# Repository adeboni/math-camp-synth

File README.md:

# Burning Man Math Camp Synths
2022: Pendulum

2023: Jukebox

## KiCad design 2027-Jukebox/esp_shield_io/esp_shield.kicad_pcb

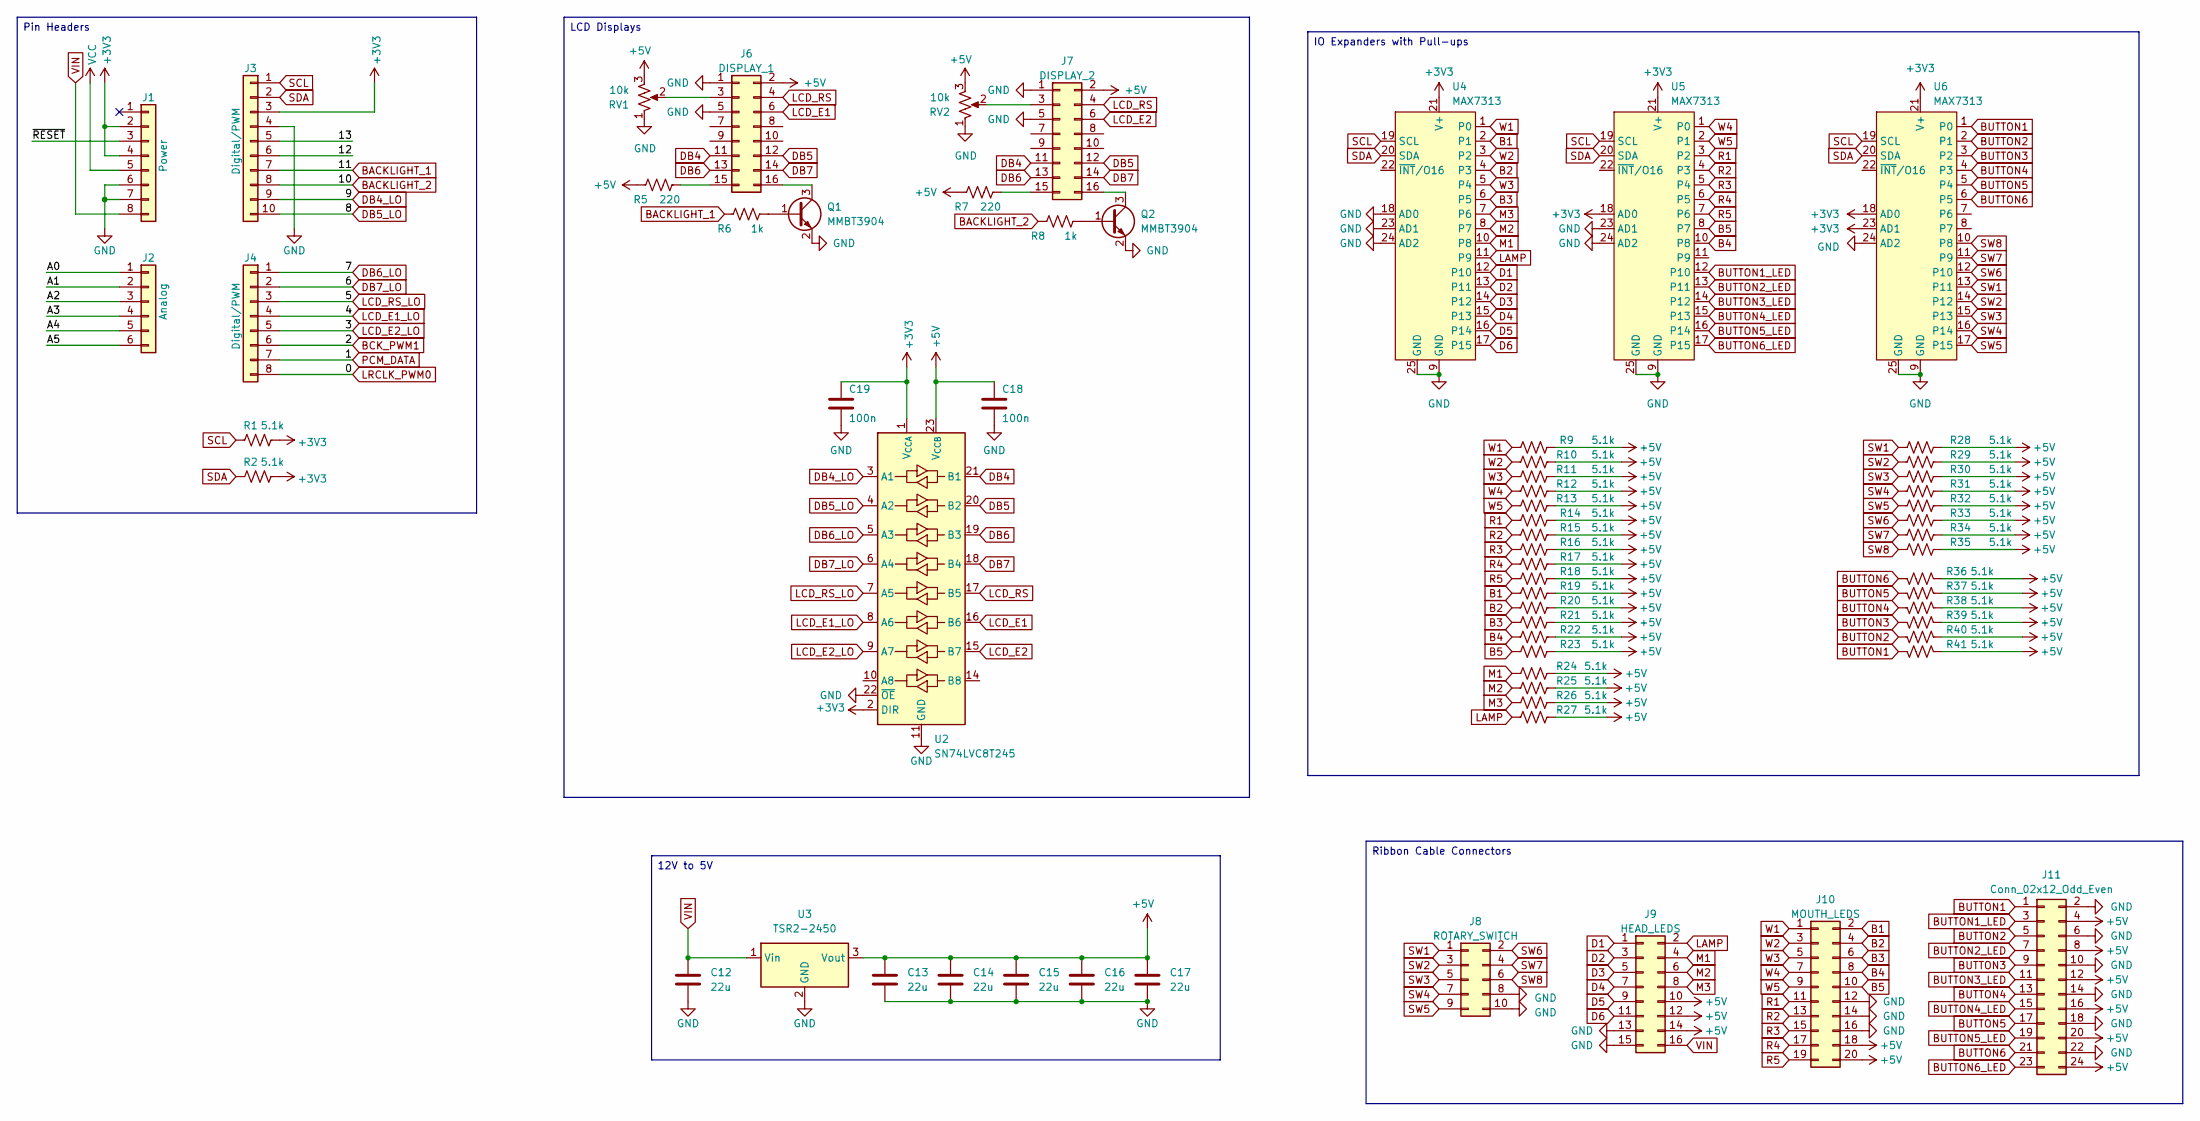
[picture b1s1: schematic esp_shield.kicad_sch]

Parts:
C12, C13, C14, C15, C16, C17: 22u; C_1206_3216Metric
C18, C19: 100n; C_0603_1608Metric
J1: Power; PinSocket_1x08_P2.54mm_Vertical
J2: Analog; PinSocket_1x06_P2.54mm_Vertical
J3: Digital/PWM; PinSocket_1x10_P2.54mm_Vertical
J4: Digital/PWM; PinSocket_1x08_P2.54mm_Vertical
J6: DISPLAY_1; IDC-Header_2x08_P2.54mm_Vertical
J7: DISPLAY_2; IDC-Header_2x08_P2.54mm_Vertical
J8: ROTARY_SWITCH; IDC-Header_2x05_P2.54mm_Vertical
J9: HEAD_LEDS; IDC-Header_2x08_P2.54mm_Vertical
J10: MOUTH_LEDS; IDC-Header_2x10_P2.54mm_Vertical
J11: Conn_02x12_Odd_Even; IDC-Header_2x12_P2.54mm_Vertical
Q1, Q2: MMBT3904; SOT-23
R1, R2, R9, R10, R11, R12, R13, R14, R15, R16, R17, R18, R19, R20, R21, R22, R23, R24, R25, R26, R27, R28, R29, R30, R31, R32, R33, R34, R35, R36, R37, R38, R39, R40, R41: 5.1k; R_0603_1608Metric
R5, R7: 220; R_0603_1608Metric
R6, R8: 1k; R_0603_1608Metric
RV1, RV2: 10k; Potentiometer_Bourns_3314G_Vertical
U2: SN74LVC8T245; TSSOP-24_4.4x7.8mm_P0.65mm
U3: TSR2-2450; Converter_DCDC_TRACO_TSR2-xxxx_THT
U4, U5, U6: MAX7313; TQFN-24-1EP_4x4mm_P0.5mm_EP2.6x2.6mm_ThermalVias

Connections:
+3V3: C19.1, J1.2, J1.4, J3.3, R1.2, R2.2, U2.1 (V_{CCA}), U2.2 (DIR), U4.21 (V+), U5.18 (AD0), U5.21 (V+), U6.18 (AD0), U6.21 (V+), U6.23 (AD1)
+5V: C13.1, C14.1, C15.1, C16.1, C17.1, C18.1, J6.2, J7.2, J9.10, J9.12, J9.14, J10.18, J10.20, J11.4, J11.8, J11.12, J11.16, J11.20, J11.24, R5.1, R7.1, R9.2, R10.2, R11.2, R12.2, R13.2, R14.2, R15.2, R16.2, R17.2, R18.2, R19.2, R20.2, R21.2, R22.2, R23.2, R24.2, R25.2, R26.2, R27.2, R28.2, R29.2, R30.2, R31.2, R32.2, R33.2, R34.2, R35.2, R36.2, R37.2, R38.2, R39.2, R40.2, R41.2, RV1.3, RV2.3, U2.23 (V_{CCB}), U2.24 (V_{CCB}), U3.3 (Vout)
/12: J3.6
/13: J3.5
/A0: J2.1
/A1: J2.2
/A2: J2.3
/A3: J2.4
/A4: J2.5
/A5: J2.6
/~RESET: J1.3
B1: J10.2, R19.1, U4.2 (P1)
B2: J10.4, R20.1, U4.4 (P3)
B3: J10.6, R21.1, U4.6 (P5)
B4: J10.8, R22.1, U5.10 (P8)
B5: J10.10, R23.1, U5.8 (P7)
BACKLIGHT_1: J3.7, R6.1
BACKLIGHT_2: J3.8, R8.1
BCK_PWM1: J4.6
BUTTON1: J11.1, R41.1, U6.1 (P0)
BUTTON1_LED: J11.3, U5.12 (P10)
BUTTON2: J11.5, R40.1, U6.2 (P1)
BUTTON2_LED: J11.7, U5.13 (P11)
BUTTON3: J11.9, R39.1, U6.3 (P2)
BUTTON3_LED: J11.11, U5.14 (P12)
BUTTON4: J11.13, R38.1, U6.4 (P3)
BUTTON4_LED: J11.15, U5.15 (P13)
BUTTON5: J11.17, R37.1, U6.5 (P4)
BUTTON5_LED: J11.19, U5.16 (P14)
BUTTON6: J11.21, R36.1, U6.6 (P5)
BUTTON6_LED: J11.23, U5.17 (P15)
D1: J9.1, U4.12 (P10)
D2: J9.3, U4.13 (P11)
D3: J9.5, U4.14 (P12)
D4: J9.7, U4.15 (P13)
D5: J9.9, U4.16 (P14)
D6: J9.11, U4.17 (P15)
DB4: J6.11, J7.11, U2.21 (B1)
DB4_LO: J3.9, U2.3 (A1)
DB5: J6.12, J7.12, U2.20 (B2)
DB5_LO: J3.10, U2.4 (A2)
DB6: J6.13, J7.13, U2.19 (B3)
DB6_LO: J4.1, U2.5 (A3)
DB7: J6.14, J7.14, U2.18 (B4)
DB7_LO: J4.2, U2.6 (A4)
GND: C12.2, C13.2, C14.2, C15.2, C16.2, C17.2, C18.2, C19.2, J1.6, J1.7, J3.4, J6.1, J6.5, J7.1, J7.5, J8.8, J8.10, J9.13, J9.15, J10.12, J10.14, J10.16, J11.2, J11.6, J11.10, J11.14, J11.18, J11.22, Q1.2 (E), Q2.2 (E), RV1.1, RV2.1, U2.11 (GND), U2.12 (GND), U2.13 (GND), U2.22 (~OE), U3.2 (GND), U4.9 (GND), U4.18 (AD0), U4.23 (AD1), U4.24 (AD2), U4.25 (GND), U5.9 (GND), U5.23 (AD1), U5.24 (AD2), U5.25 (GND), U6.9 (GND), U6.24 (AD2), U6.25 (GND)
LAMP: J9.2, R27.1, U4.11 (P9)
LCD_E1: J6.6, U2.16 (B6)
LCD_E1_LO: J4.4, U2.8 (A6)
LCD_E2: J7.6, U2.15 (B7)
LCD_E2_LO: J4.5, U2.9 (A7)
LCD_RS: J6.4, J7.4, U2.17 (B5)
LCD_RS_LO: J4.3, U2.7 (A5)
LRCLK_PWM0: J4.8
M1: J9.4, R24.1, U4.10 (P8)
M2: J9.6, R25.1, U4.8 (P7)
M3: J9.8, R26.1, U4.7 (P6)
unnamed: J6.3, RV1.2
unnamed: J6.15, R5.2
unnamed: J6.16, Q1.3 (C)
unnamed: J7.3, RV2.2
unnamed: J7.15, R7.2
unnamed: J7.16, Q2.3 (C)
unnamed: Q1.1 (B), R6.2
unnamed: Q2.1 (B), R8.2
PCM_DATA: J4.7
R1: J10.11, R14.1, U5.3 (P2)
R2: J10.13, R15.1, U5.4 (P3)
R3: J10.15, R16.1, U5.5 (P4)
R4: J10.17, R17.1, U5.6 (P5)
R5: J10.19, R18.1, U5.7 (P6)
SCL: J3.1, R1.1, U4.19 (SCL), U5.19 (SCL), U6.19 (SCL)
SDA: J3.2, R2.1, U4.20 (SDA), U5.20 (SDA), U6.20 (SDA)
SW1: J8.1, R28.1, U6.13 (P11)
SW2: J8.3, R29.1, U6.14 (P12)
SW3: J8.5, R30.1, U6.15 (P13)
SW4: J8.7, R31.1, U6.16 (P14)
SW5: J8.9, R32.1, U6.17 (P15)
SW6: J8.2, R33.1, U6.12 (P10)
SW7: J8.4, R34.1, U6.11 (P9)
SW8: J8.6, R35.1, U6.10 (P8)
VCC: J1.5
VIN: C12.1, J1.8, J9.16, U3.1 (Vin)
W1: J10.1, R9.1, U4.1 (P0)
W2: J10.3, R10.1, U4.3 (P2)
W3: J10.5, R11.1, U4.5 (P4)
W4: J10.7, R12.1, U5.1 (P0)
W5: J10.9, R13.1, U5.2 (P1)

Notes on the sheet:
Ribbon Cable Connectors
LCD Displays
IO Expanders with Pull-ups
12V to 5V
Pin Headers

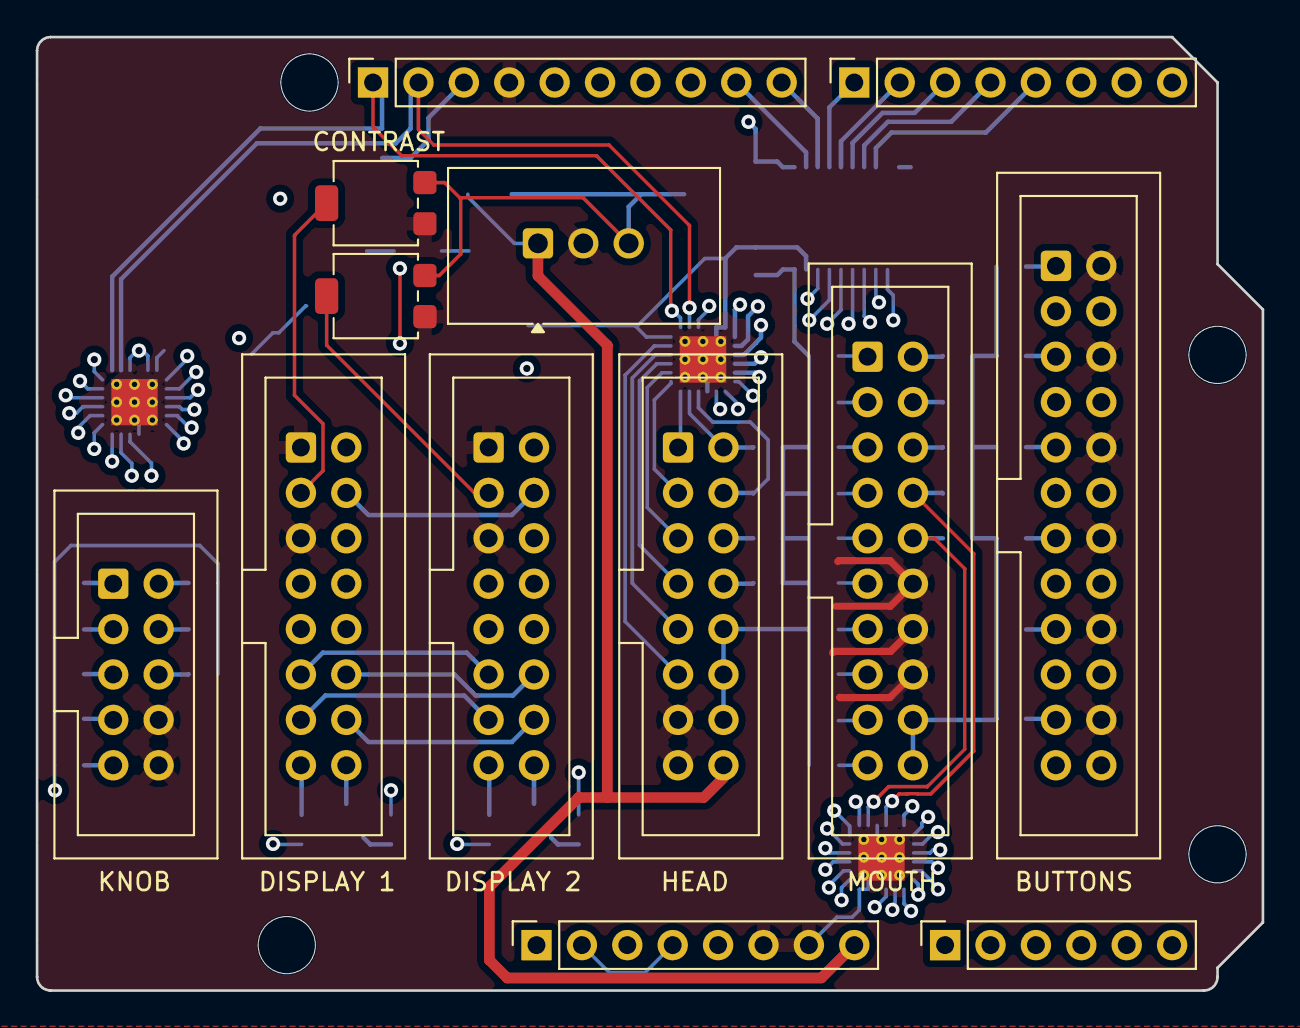
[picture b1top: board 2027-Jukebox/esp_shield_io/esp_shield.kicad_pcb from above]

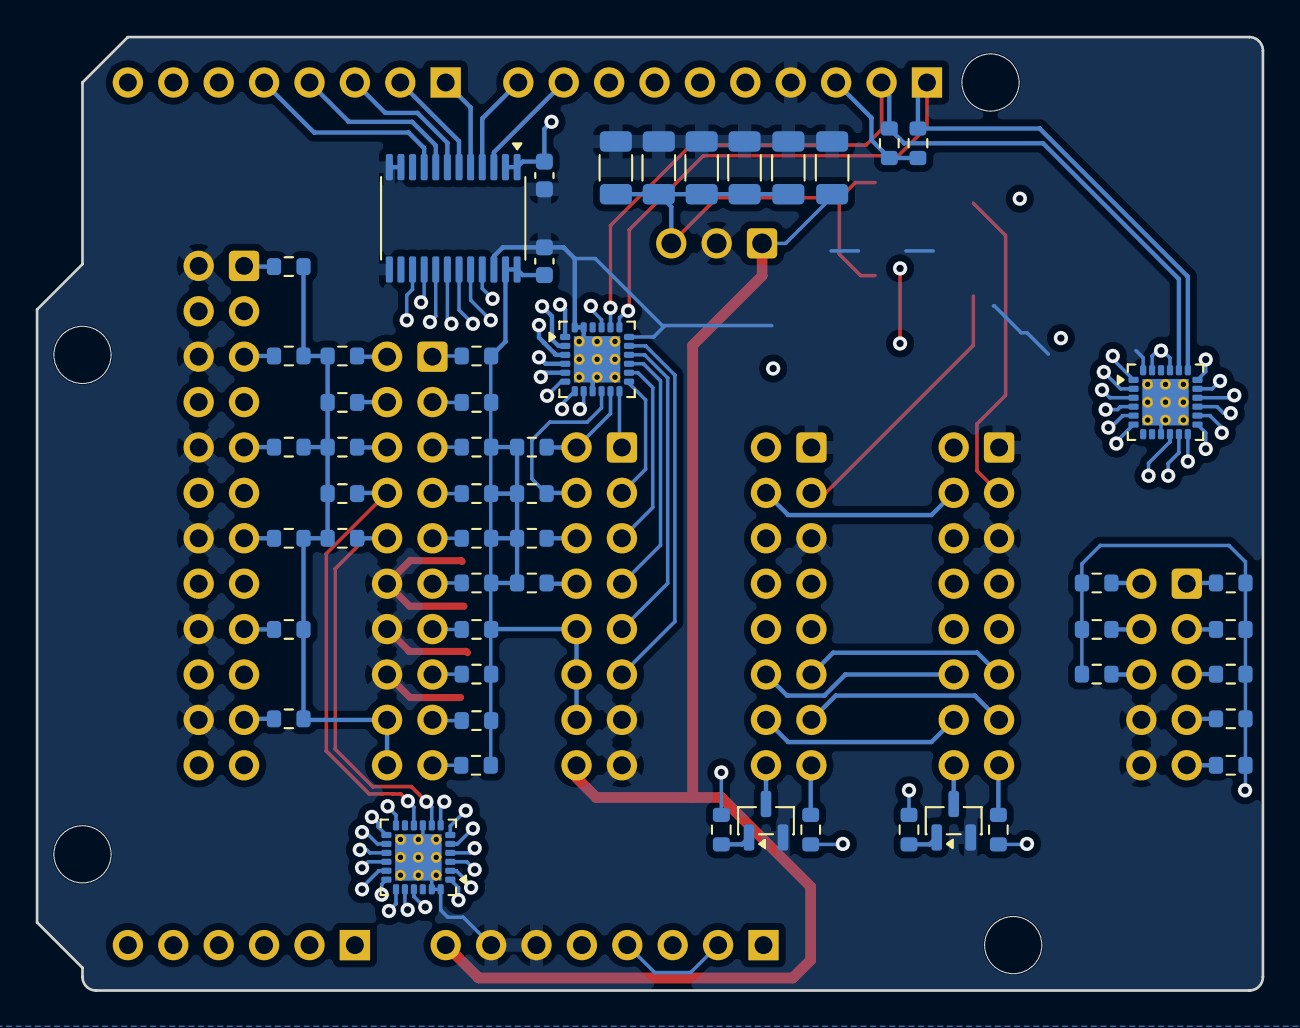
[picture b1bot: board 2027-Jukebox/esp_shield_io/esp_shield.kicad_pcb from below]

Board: 4 copper layers, 68.6 x 53.3 mm, 70 parts (53 on the bottom side), 75 nets.

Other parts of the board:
MH1, MH2, MH3, MH4: MountingHole_3.2mm

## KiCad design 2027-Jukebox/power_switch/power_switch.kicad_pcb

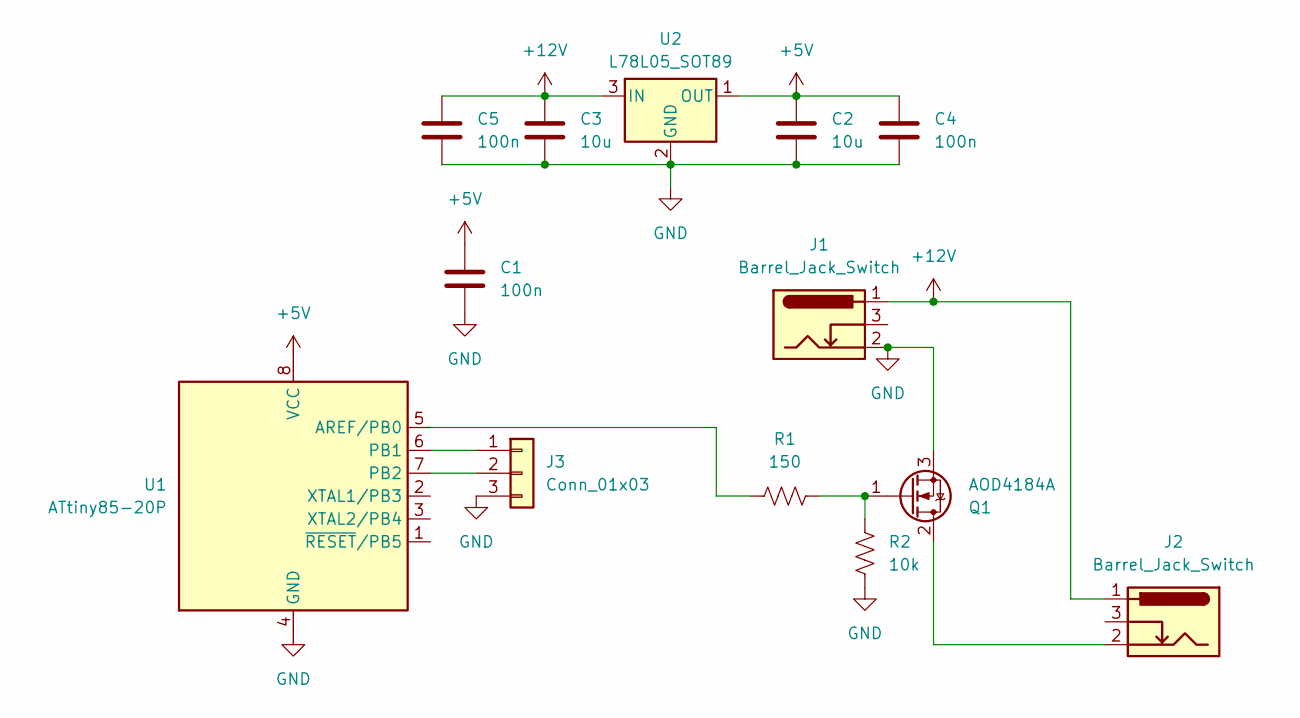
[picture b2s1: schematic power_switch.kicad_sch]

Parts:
C1, C4, C5: 100n; C_0603_1608Metric
C2, C3: 10u; C_0603_1608Metric
J1, J2: Barrel_Jack_Switch; BarrelJack_Horizontal
J3: Conn_01x03; JST_XH_S3B-XH-A_1x03_P2.50mm_Horizontal
Q1: AOD4184A; TO-252-2
R1: 150; R_0603_1608Metric
R2: 10k; R_0603_1608Metric
U1: ATtiny85-20P; DIP-8_W7.62mm
U2: L78L05_SOT89; SOT-89-3

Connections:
+5V: C1.1, C2.1, C4.1, U1.8 (VCC), U2.1 (OUT)
+12V: C3.1, C5.1, J1.1, J2.1, U2.3 (IN)
GND: C1.2, C2.2, C3.2, C4.2, C5.2, J1.2, J3.3, Q1.3 (S), R2.1, U1.4 (GND), U2.2 (GND)
unnamed: J3.1, U1.6 (PB1)
unnamed: J3.2, U1.7 (PB2)
unnamed: J2.2, Q1.2 (D)
unnamed: Q1.1 (G), R1.2, R2.2
unnamed: R1.1, U1.5 (AREF/PB0)

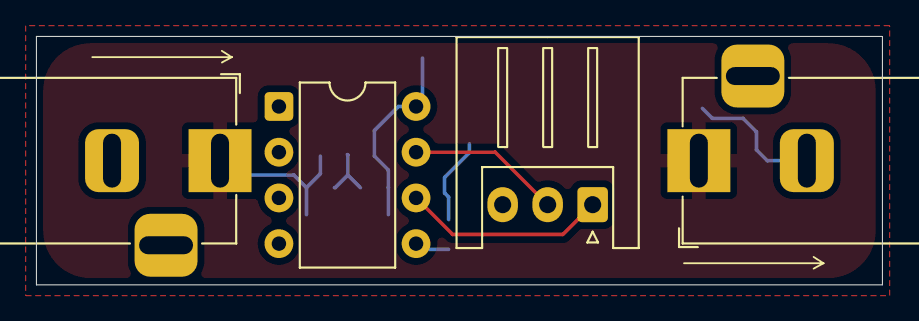
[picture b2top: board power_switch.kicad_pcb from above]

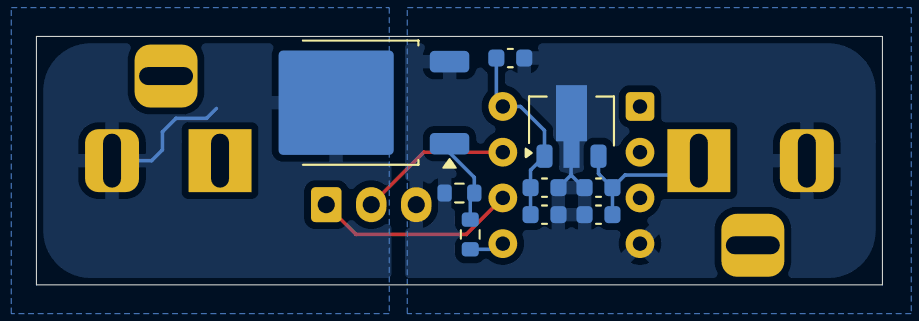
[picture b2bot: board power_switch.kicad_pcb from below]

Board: 2 copper layers, 47.0 x 13.8 mm, 13 parts (9 on the bottom side), 8 nets.

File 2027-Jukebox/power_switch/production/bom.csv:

Designator,Footprint,Quantity,Value,LCSC Part #
"C1, C4, C5",0603,3,100n,
"C2, C3",0603,2,10u,
"J1, J2",BarrelJack_Horizontal,2,Barrel_Jack_Switch,
J3,JST_XH_S3B-XH-A_1x03_P2.50mm_Horizontal,1,Conn_01x03,
Q1,TO-252-2,1,AOD4184A,
R1,0603,1,150,
R2,0603,1,10k,
U1,DIP-8_W7.62mm,1,ATtiny85-20P,
U2,SOT-89-3,1,L78L05_SOT89,

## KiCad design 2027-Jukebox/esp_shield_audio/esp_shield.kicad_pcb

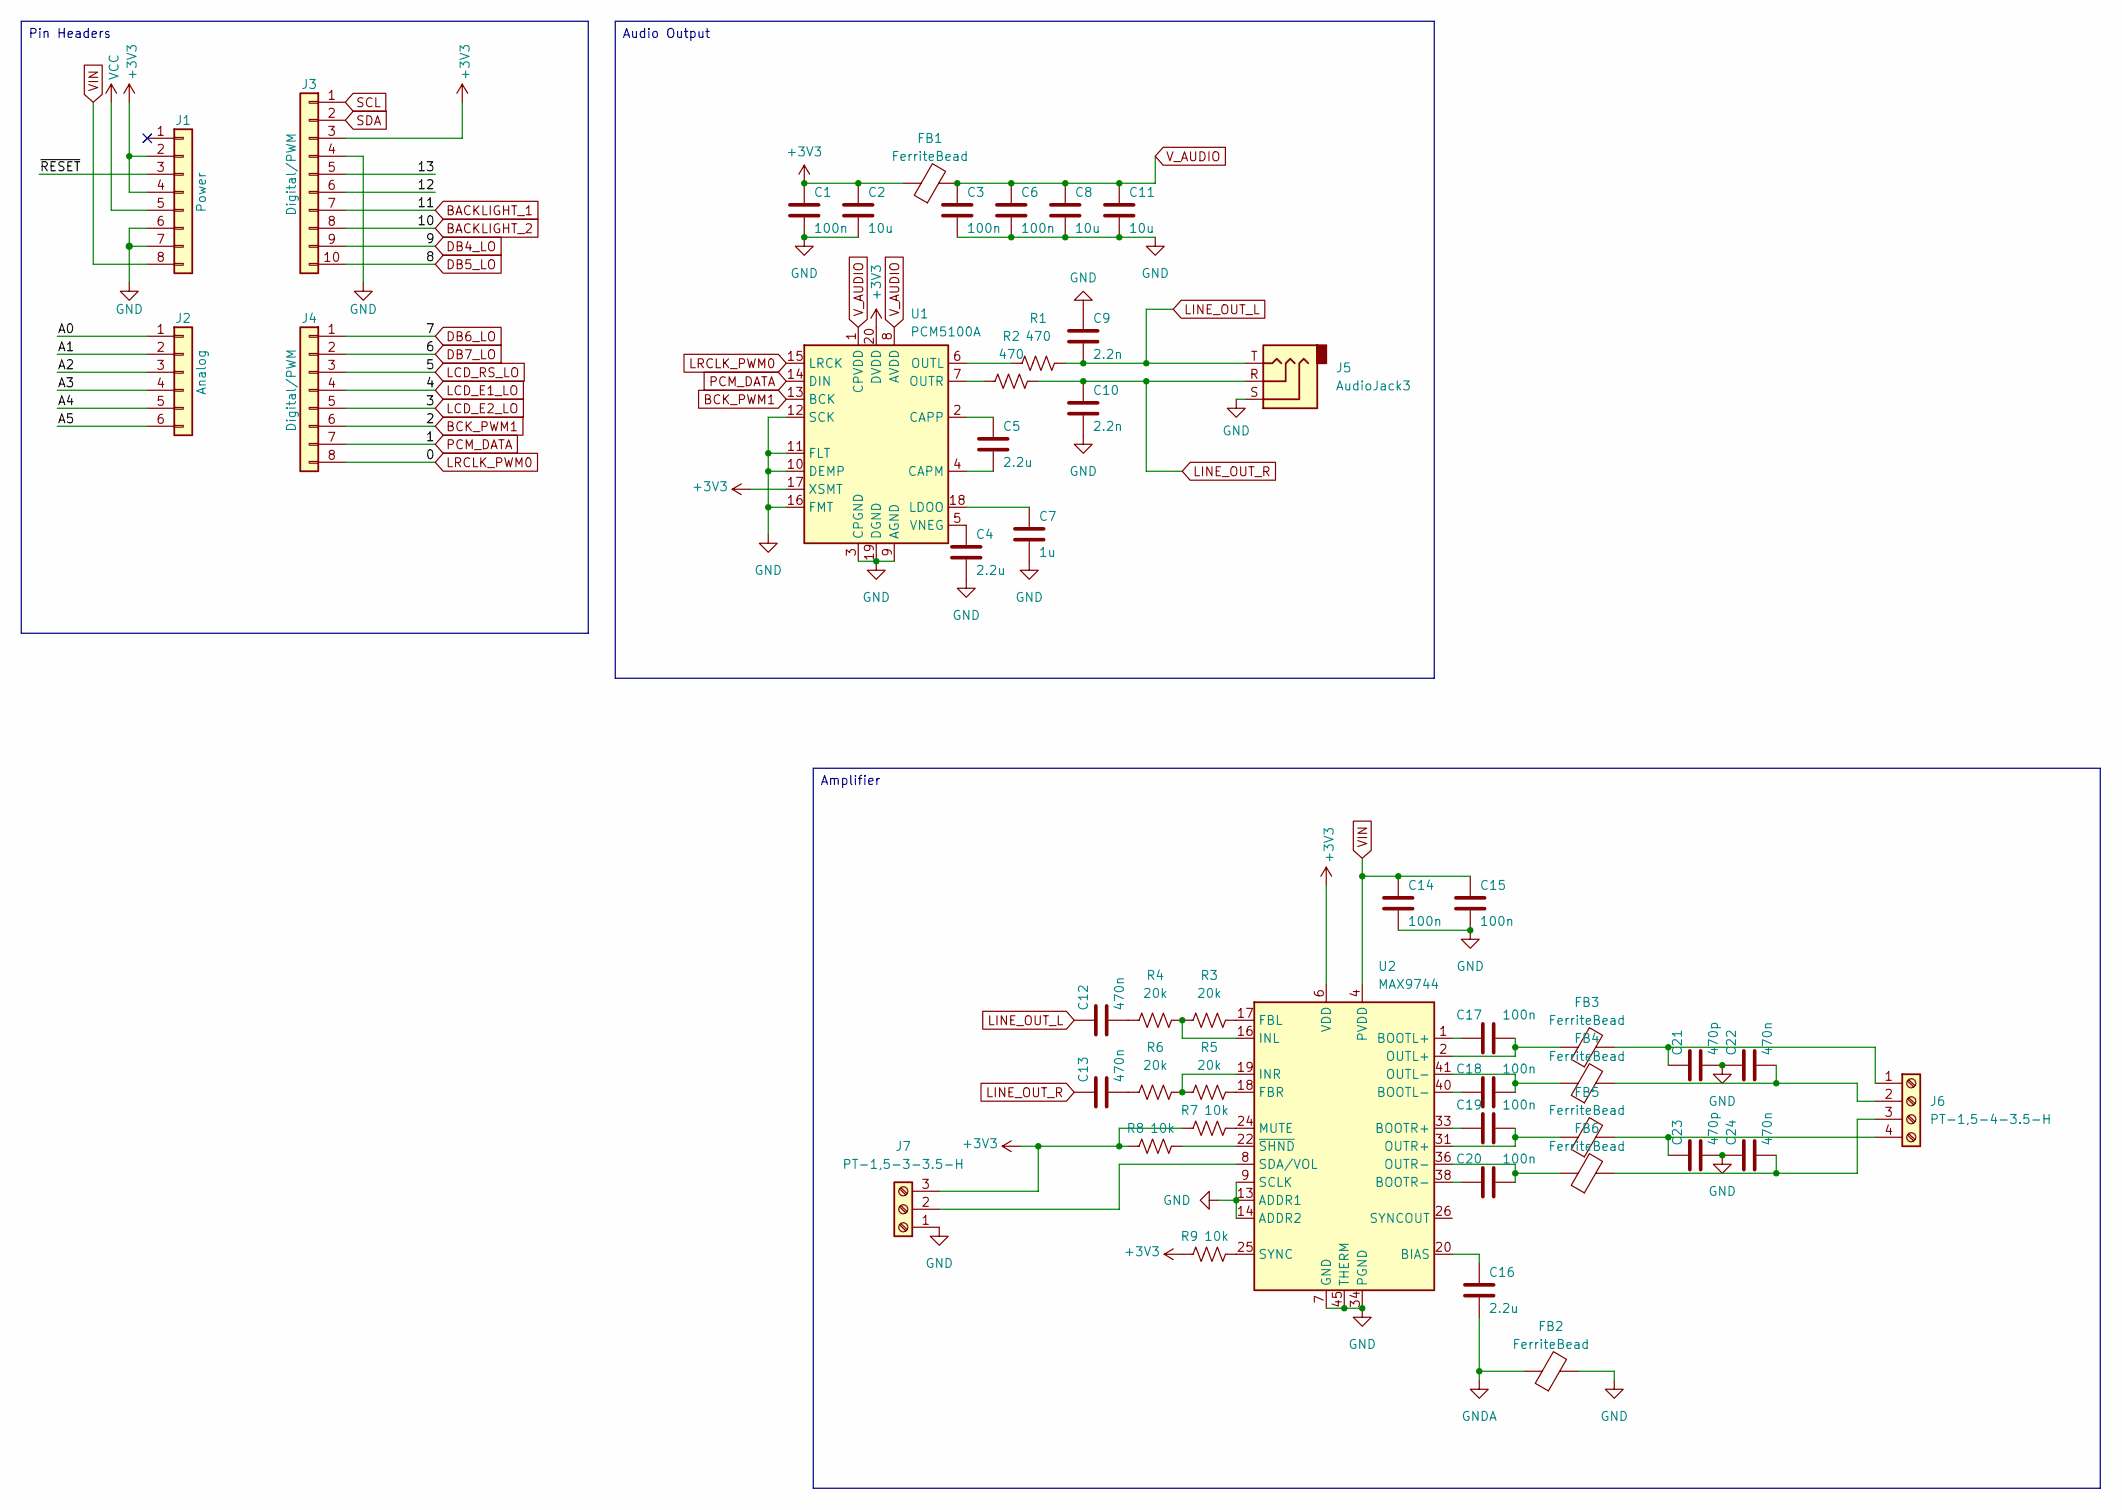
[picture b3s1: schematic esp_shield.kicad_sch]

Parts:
C1, C3, C6, C14, C15, C17, C18, C19, C20: 100n; C_0603_1608Metric
C2, C8, C11: 10u; C_0603_1608Metric
C4, C5, C16: 2.2u; C_0603_1608Metric
C7: 1u; C_0603_1608Metric
C9, C10: 2.2n; C_0603_1608Metric
C12, C13, C22, C24: 470n; C_0603_1608Metric
C21, C23: 470p; C_0603_1608Metric
FB1, FB2, FB3, FB4, FB5, FB6: FerriteBead; L_0603_1608Metric
J1: Power; PinSocket_1x08_P2.54mm_Vertical
J2: Analog; PinSocket_1x06_P2.54mm_Vertical
J3: Digital/PWM; PinSocket_1x10_P2.54mm_Vertical
J4: Digital/PWM; PinSocket_1x08_P2.54mm_Vertical
J5: AudioJack3; Jack_3.5mm_CUI_SJ-3523-SMT_Horizontal
J6: PT-1,5-4-3.5-H; TerminalBlock_Phoenix_PT-1,5-4-3.5-H_1x04_P3.50mm_Horizontal
J7: PT-1,5-3-3.5-H; TerminalBlock_Phoenix_PT-1,5-3-3.5-H_1x03_P3.50mm_Horizontal
R1, R2: 470; R_0603_1608Metric
R3, R4, R5, R6: 20k; R_0603_1608Metric
R7, R8, R9: 10k; R_0603_1608Metric
U1: PCM5100A; TSSOP-20_4.4x6.5mm_P0.65mm
U2: MAX9744; TQFN-44-1EP_7x7mm_P0.5mm_EP4.7x4.7mm_ThermalVias

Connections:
+3V3: C1.1, C2.1, FB1.1, J1.2, J1.4, J3.3, J7.3, R7.2, R8.2, R9.2, U1.17 (XSMT), U1.20 (DVDD), U2.6 (VDD), U2.10 (VDD), U2.21 (VDD), U2.28 (VDD)
/12: J3.6
/13: J3.5
/A0: J2.1
/A1: J2.2
/A2: J2.3
/A3: J2.4
/A4: J2.5
/A5: J2.6
/~RESET: J1.3
BACKLIGHT_1: J3.7
BACKLIGHT_2: J3.8
BCK_PWM1: J4.6, U1.13 (BCK)
DB4_LO: J3.9
DB5_LO: J3.10
DB6_LO: J4.1
DB7_LO: J4.2
GND: C1.2, C2.2, C3.2, C4.2, C6.2, C7.2, C8.2, C9.1, C10.2, C11.2, C14.2, C15.2, C21.2, C22.1, C23.2, C24.1, FB2.2, J1.6, J1.7, J3.4, J5.S, J7.1, U1.3 (CPGND), U1.9 (AGND), U1.10 (DEMP), U1.11 (FLT), U1.12 (SCK), U1.16 (FMT), U1.19 (DGND), U2.7 (GND), U2.9 (SCLK), U2.11 (GND), U2.12 (GND), U2.13 (ADDR1), U2.14 (ADDR2), U2.15 (GND), U2.27 (GND), U2.34 (PGND), U2.35 (PGND), U2.39 (PGND), U2.43 (PGND), U2.44 (PGND), U2.45 (THERM)
GNDA: C16.2, FB2.1
LCD_E1_LO: J4.4
LCD_E2_LO: J4.5
LCD_RS_LO: J4.3
LINE_OUT_L: C9.2, C12.1, J5.T, R1.2
LINE_OUT_R: C10.1, C13.1, J5.R, R2.1
LRCLK_PWM0: J4.8, U1.15 (LRCK)
unnamed: C12.2, R4.2
unnamed: C13.2, R6.2
unnamed: C17.2, FB3.1, U2.2 (OUTL+), U2.3 (OUTL+)
unnamed: C18.2, FB4.1, U2.41 (OUTL-), U2.42 (OUTL-)
unnamed: C19.2, FB5.1, U2.31 (OUTR+), U2.32 (OUTR+)
unnamed: C20.2, FB6.1, U2.36 (OUTR-), U2.37 (OUTR-)
unnamed: C21.1, FB3.2, J6.1
unnamed: C22.2, FB4.2, J6.2
unnamed: C24.2, FB6.2, J6.3
unnamed: C23.1, FB5.2, J6.4
unnamed: J7.2, U2.8 (SDA/VOL)
unnamed: C5.2, U1.4 (CAPM)
unnamed: C5.1, U1.2 (CAPP)
unnamed: C7.1, U1.18 (LDOO)
unnamed: R1.1, U1.6 (OUTL)
unnamed: R2.2, U1.7 (OUTR)
unnamed: C4.1, U1.5 (VNEG)
unnamed: C16.1, U2.20 (BIAS)
unnamed: C17.1, U2.1 (BOOTL+)
unnamed: C18.1, U2.40 (BOOTL-)
unnamed: C19.1, U2.33 (BOOTR+)
unnamed: C20.1, U2.38 (BOOTR-)
unnamed: R3.1, U2.17 (FBL)
unnamed: R5.1, U2.18 (FBR)
unnamed: R3.2, R4.1, U2.16 (INL)
unnamed: R5.2, R6.1, U2.19 (INR)
unnamed: R7.1, U2.24 (MUTE)
unnamed: R9.1, U2.25 (SYNC)
unnamed: R8.1, U2.22 (~SHND)
PCM_DATA: J4.7, U1.14 (DIN)
SCL: J3.1
SDA: J3.2
VCC: J1.5
VIN: C14.1, C15.1, J1.8, U2.4 (PVDD), U2.5 (PVDD), U2.29 (PVDD), U2.30 (PVDD)
V_AUDIO: C3.1, C6.1, C8.1, C11.1, FB1.2, U1.1 (CPVDD), U1.8 (AVDD)

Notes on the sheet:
Audio Output
Amplifier
Pin Headers

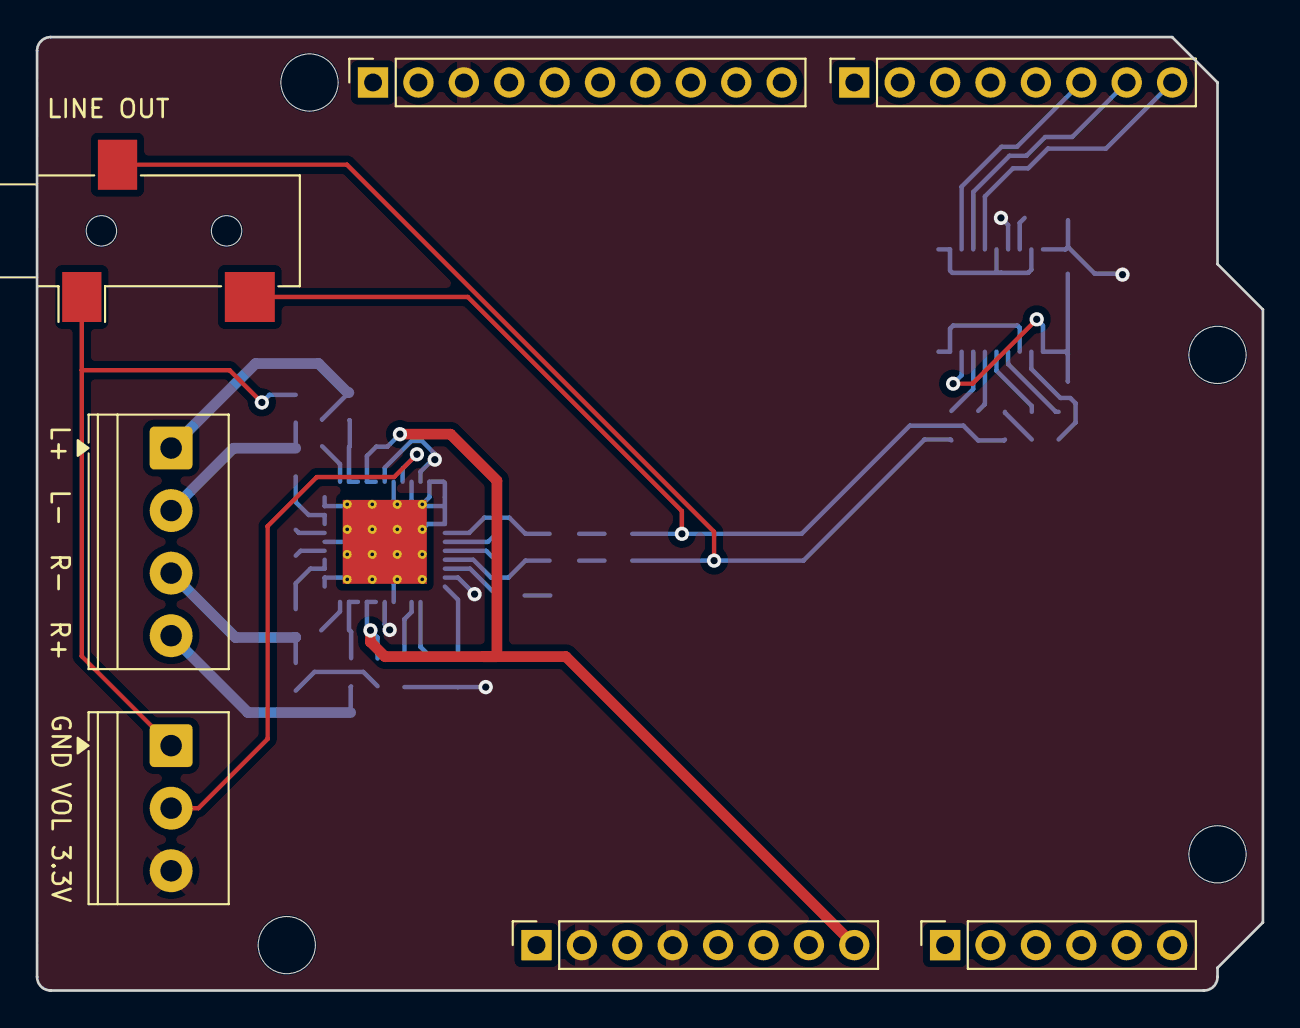
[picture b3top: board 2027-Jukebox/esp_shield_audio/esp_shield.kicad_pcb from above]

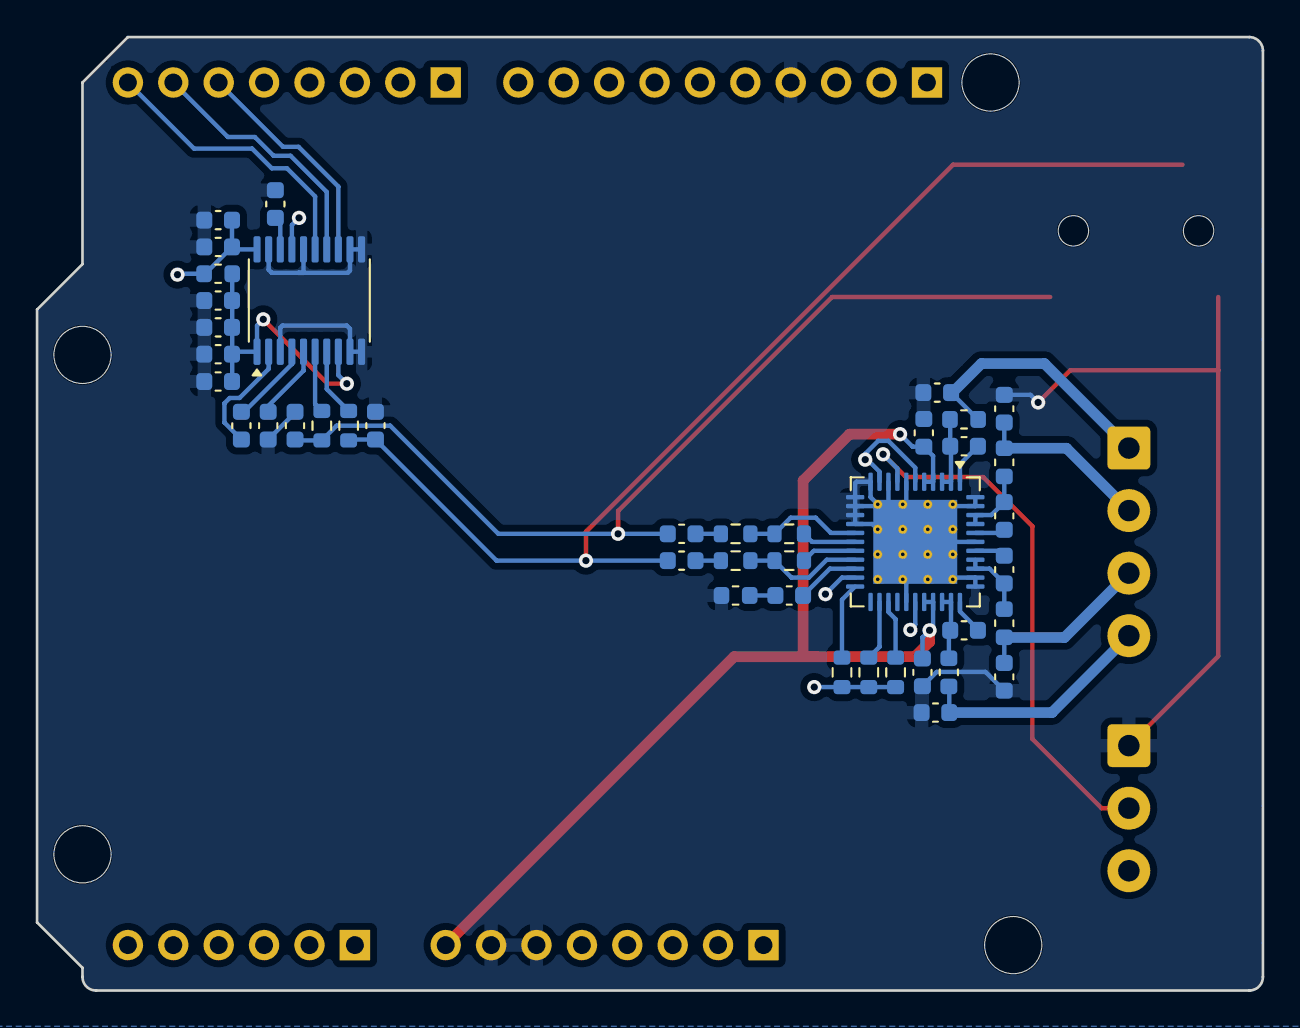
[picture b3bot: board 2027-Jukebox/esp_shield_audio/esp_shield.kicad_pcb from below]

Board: 2 copper layers, 68.6 x 53.3 mm, 52 parts (41 on the bottom side), 39 nets.

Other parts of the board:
MH1, MH2, MH3, MH4: MountingHole_3.2mm

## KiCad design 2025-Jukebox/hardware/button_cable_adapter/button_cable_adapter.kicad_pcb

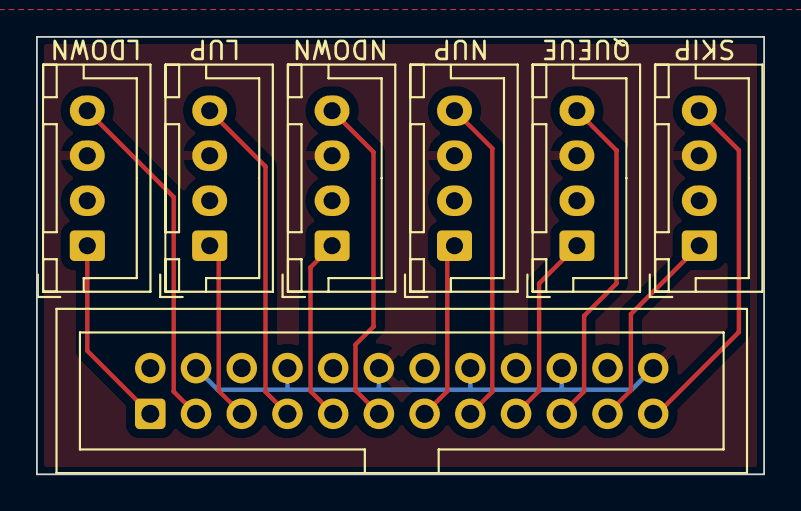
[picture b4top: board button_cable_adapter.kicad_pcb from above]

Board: 2 copper layers, 40.4 x 24.3 mm, 7 parts (0 on the bottom side), 14 nets.

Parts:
J1: Conn_02x12_Odd_Even; IDC-Header_2x12_P2.54mm_Vertical
J2: BUTTON_1; JST_XH_B4B-XH-A_1x04_P2.50mm_Vertical
J3: BUTTON_5; JST_XH_B4B-XH-A_1x04_P2.50mm_Vertical
J4: BUTTON_2; JST_XH_B4B-XH-A_1x04_P2.50mm_Vertical
J5: BUTTON_6; JST_XH_B4B-XH-A_1x04_P2.50mm_Vertical
J6: BUTTON_3; JST_XH_B4B-XH-A_1x04_P2.50mm_Vertical
J8: BUTTON_4; JST_XH_B4B-XH-A_1x04_P2.50mm_Vertical

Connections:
+5V: J1.4, J1.8, J1.12, J1.16, J1.20, J1.24, J2.3, J3.3, J4.3, J5.3, J6.3, J8.3
BUTTON1: J1.1, J2.1
BUTTON1_LED: J1.3, J2.4
BUTTON2: J1.5, J4.1
BUTTON2_LED: J1.7, J4.4
BUTTON3: J1.9, J6.1
BUTTON3_LED: J1.11, J6.4
BUTTON4: J1.13, J8.1
BUTTON4_LED: J1.15, J8.4
BUTTON5: J1.17, J3.1
BUTTON5_LED: J1.19, J3.4
BUTTON6: J1.21, J5.1
BUTTON6_LED: J1.23, J5.4
GND: J1.2, J1.6, J1.10, J1.14, J1.18, J1.22, J2.2, J3.2, J4.2, J5.2, J6.2, J8.2

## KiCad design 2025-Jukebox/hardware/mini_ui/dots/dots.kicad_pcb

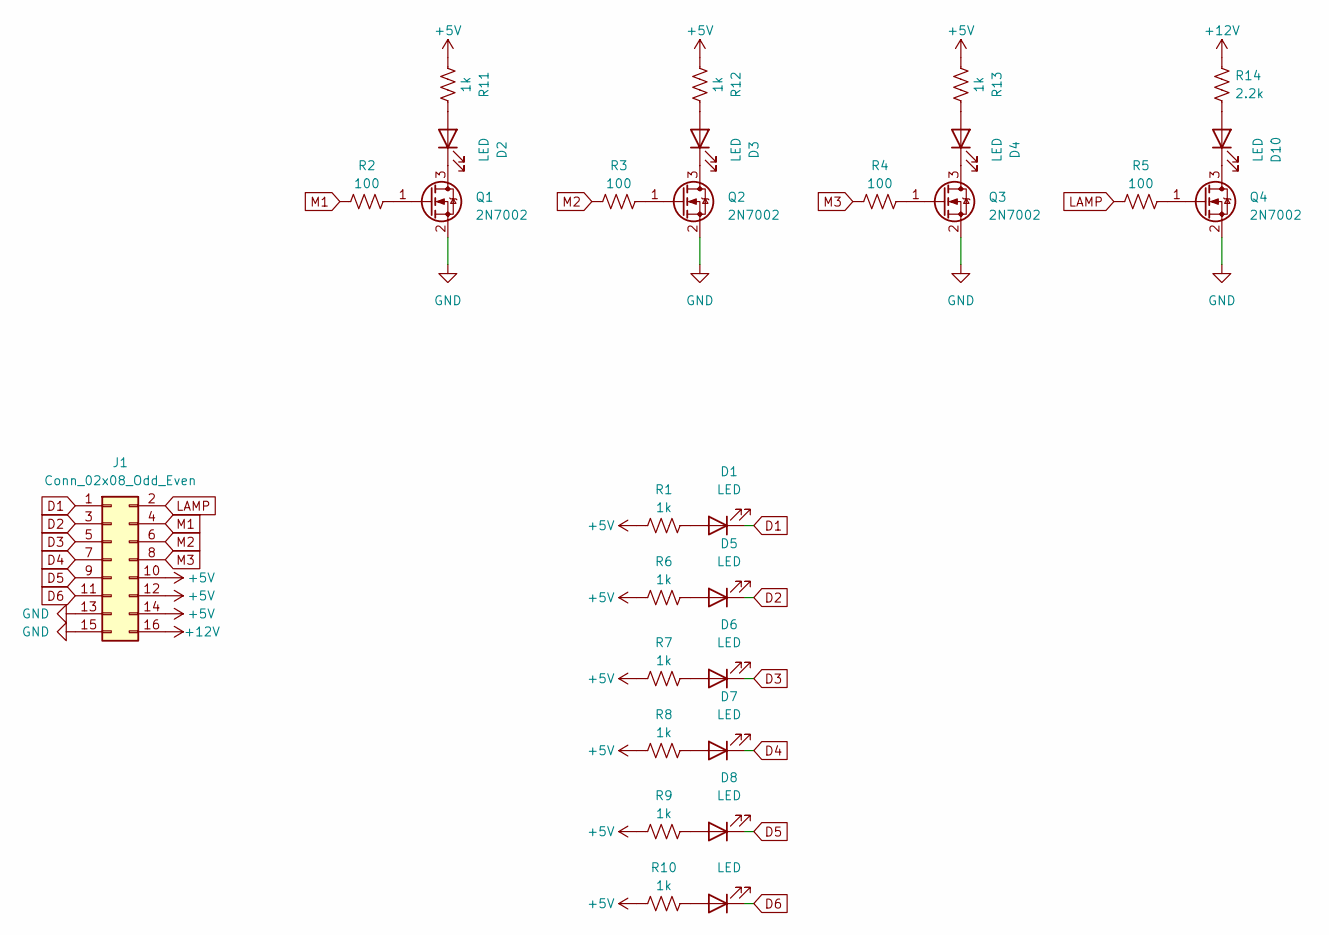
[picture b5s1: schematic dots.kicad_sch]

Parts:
D1, D2, D3, D4, D5, D6, D7, D8, D9, D10: LED; LED_0603_1608Metric
J1: Conn_02x08_Odd_Even; PinSocket_2x08_P2.54mm_Vertical_SMD
Q1, Q2, Q3, Q4: 2N7002; SOT-23
R1, R6, R7, R8, R9, R10, R11, R12, R13: 1k; R_0603_1608Metric
R2, R3, R4, R5: 100; R_0603_1608Metric
R14: 2.2k; R_0603_1608Metric

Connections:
+5V: J1.10, J1.12, J1.14, R1.1, R6.1, R7.1, R8.1, R9.1, R10.1, R11.1, R12.1, R13.1
+12V: J1.16, R14.1
D1: D1.1 (K), J1.1
D2: D5.1 (K), J1.3
D3: D6.1 (K), J1.5
D4: D7.1 (K), J1.7
D5: D8.1 (K), J1.9
D6: D9.1 (K), J1.11
GND: J1.13, J1.15, Q1.2 (S), Q2.2 (S), Q3.2 (S), Q4.2 (S)
LAMP: J1.2, R5.1
M1: J1.4, R2.1
M2: J1.6, R3.1
M3: J1.8, R4.1
unnamed: D1.2 (A), R1.2
unnamed: D2.2 (A), R11.2
unnamed: D2.1 (K), Q1.3 (D)
unnamed: D3.2 (A), R12.2
unnamed: D3.1 (K), Q2.3 (D)
unnamed: D4.2 (A), R13.2
unnamed: D4.1 (K), Q3.3 (D)
unnamed: D5.2 (A), R6.2
unnamed: D6.2 (A), R7.2
unnamed: D7.2 (A), R8.2
unnamed: D8.2 (A), R9.2
unnamed: D9.2 (A), R10.2
unnamed: D10.2 (A), R14.2
unnamed: D10.1 (K), Q4.3 (D)
unnamed: Q1.1 (G), R2.2
unnamed: Q2.1 (G), R3.2
unnamed: Q3.1 (G), R4.2
unnamed: Q4.1 (G), R5.2

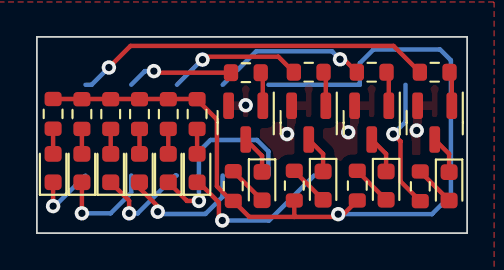
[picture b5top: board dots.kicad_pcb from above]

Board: 2 copper layers, 23.9 x 10.9 mm, 29 parts (1 on the bottom side), 31 nets.
